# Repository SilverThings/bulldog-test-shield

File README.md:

# bulldog-test-shield
A testing shield for Bulldog testing for mocking real-world devices

Repository for .ino files, KiCad files, docs ...

# Prototype

Arduino Pro Mini clone BTE13-010 (3v3)

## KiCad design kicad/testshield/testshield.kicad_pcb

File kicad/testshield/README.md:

Only I2C is supported in this design. I am trying to find a way to fit raspberry, cubieboard and beaglebone with one connector. I'm not sure it's possible. Maybe with jumpers.

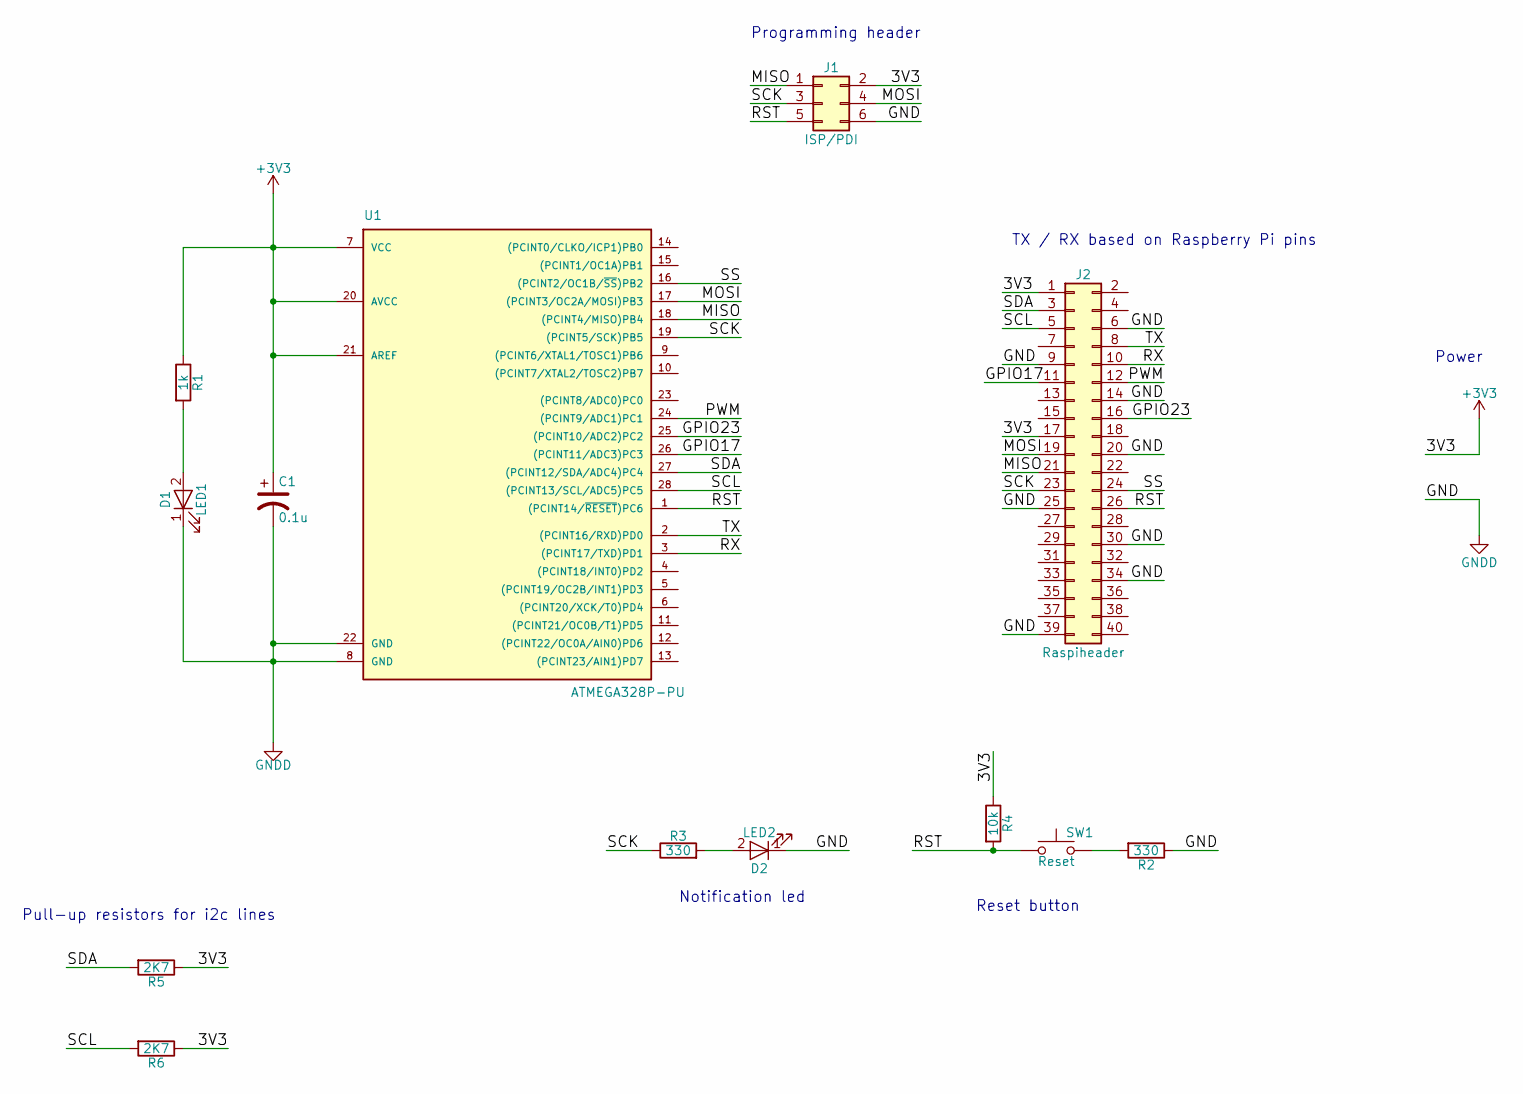
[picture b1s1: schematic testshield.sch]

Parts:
C1: 0.1u; c_elec_4x5.3
D1: LED1; LED_0805
D2: LED2; LED_0805
J1: ISP/PDI; Pin_Header_Straight_2x03
J2: Raspiheader; Pin_Header_Straight_2x20
R1: 1k; R_0603
R2, R3: 330; R_0603
R4: 10k; R_0603
R5, R6: 2K7; R_0603
SW1: Reset; SW_SPST_B3SL-1022P
U1: ATMEGA328P-PU; QFP80P900X900X120-32N

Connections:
+3V3: C1.1, J1.2, J2.1, J2.17, R1.1, R4.1, R5.1, R6.1, U1.7 (VCC), U1.20 (AVCC), U1.21 (AREF)
/GPIO17: J2.11, U1.26 ((PCINT11/ADC3)PC3)
/GPIO23: J2.16, U1.25 ((PCINT10/ADC2)PC2)
/MISO: J1.1, J2.21, U1.18 ((PCINT4/MISO)PB4)
/MOSI: J1.4, J2.19, U1.17 ((PCINT3/OC2A/MOSI)PB3)
/PWM: J2.12, U1.24 ((PCINT9/ADC1)PC1)
/RST: J1.5, J2.26, R4.2, SW1.1, U1.1 ((PCINT14/~RESET~)PC6)
/RX: J2.10, U1.3 ((PCINT17/TXD)PD1)
/SCK: J1.3, J2.23, R3.1, U1.19 ((PCINT5/SCK)PB5)
/SCL: J2.5, R6.2, U1.28 ((PCINT13/SCL/ADC5)PC5)
/SDA: J2.3, R5.2, U1.27 ((PCINT12/SDA/ADC4)PC4)
/SS: J2.24, U1.16 ((PCINT2/OC1B/~SS~)PB2)
/TX: J2.8, U1.2 ((PCINT16/RXD)PD0)
GNDD: C1.2, D1.1 (K), D2.1 (K), J1.6, J2.6, J2.9, J2.14, J2.20, J2.25, J2.30, J2.34, J2.39, R2.1, U1.8 (GND), U1.22 (GND)
unnamed: D1.2 (A), R1.2
unnamed: D2.2 (A), R3.2
unnamed: R2.2, SW1.2

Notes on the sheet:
TX / RX based on Raspberry Pi pins
Pull-up resistors for i2c lines
Programming header
Power
Reset button
Notification led

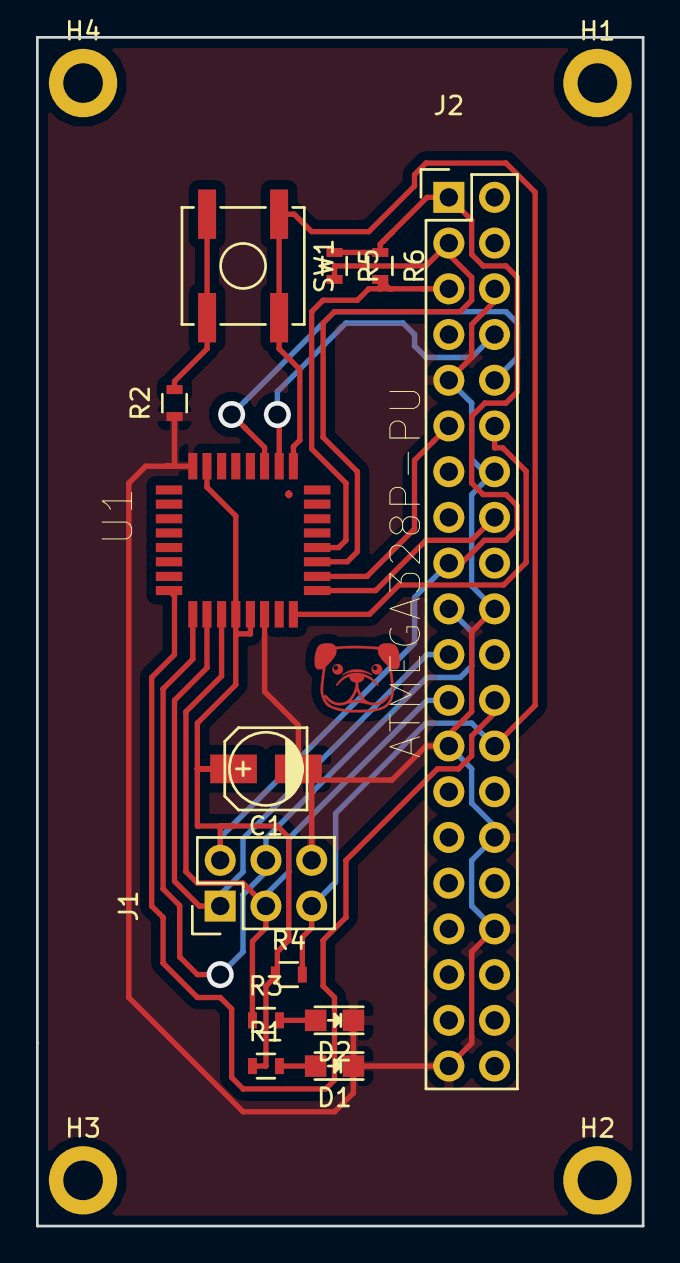
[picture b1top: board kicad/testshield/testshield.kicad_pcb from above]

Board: 2 copper layers, 33.7 x 66.0 mm, 17 parts (0 on the bottom side), 17 nets.

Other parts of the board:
H1, H2, H3, H4: MountingHole_2.2mm_M2_ISO14580_Pad

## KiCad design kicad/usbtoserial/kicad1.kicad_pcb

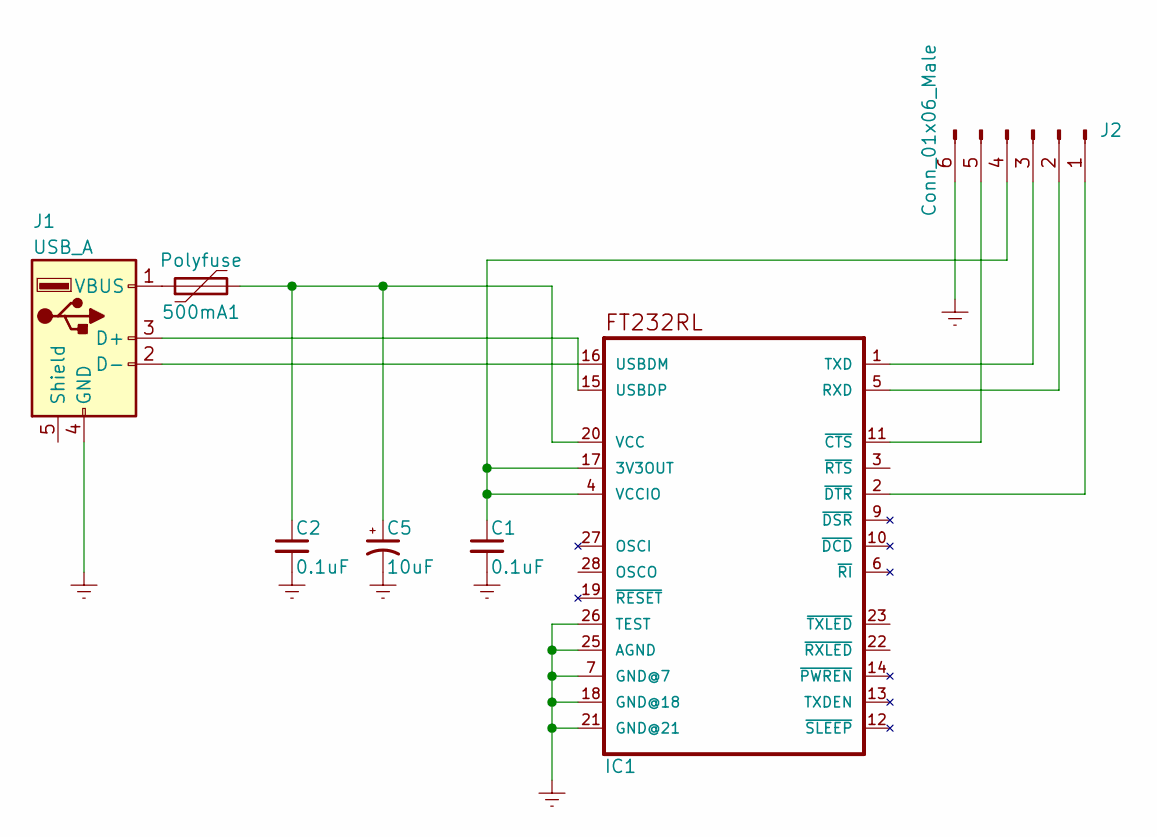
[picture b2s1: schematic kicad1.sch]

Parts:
500mA1: Polyfuse; Resistor_SMD+THTuniversal_0805to1206_RM10_HandSoldering
C1, C2: 0.1uF; C_0201
C5: 10uF; CP_Elec_3x5.3
IC1: FT232RL; SSOP28-LD
J1: USB_A; USB_Micro-B
J2: Conn_01x06_Male; Pin_Header_Angled_1x06_Pitch2.54mm

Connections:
Earth: C1.2, C2.2, C5.2, IC1.7 (GND@7), IC1.18 (GND@18), IC1.21 (GND@21), IC1.25 (AGND), IC1.26 (TEST), J1.4 (GND), J2.6
unnamed: 500mA1.1, J1.1 (VBUS)
unnamed: 500mA1.2, C2.1, C5.1, IC1.20 (VCC)
unnamed: C1.1, IC1.4 (VCCIO), IC1.17 (3V3OUT), J2.4
unnamed: IC1.1 (TXD), J2.3
unnamed: IC1.2 (~DTR~), J2.1
unnamed: IC1.5 (RXD), J2.2
unnamed: IC1.11 (~CTS~), J2.5
unnamed: IC1.15 (USBDP), J1.3 (D+)
unnamed: IC1.16 (USBDM), J1.2 (D-)

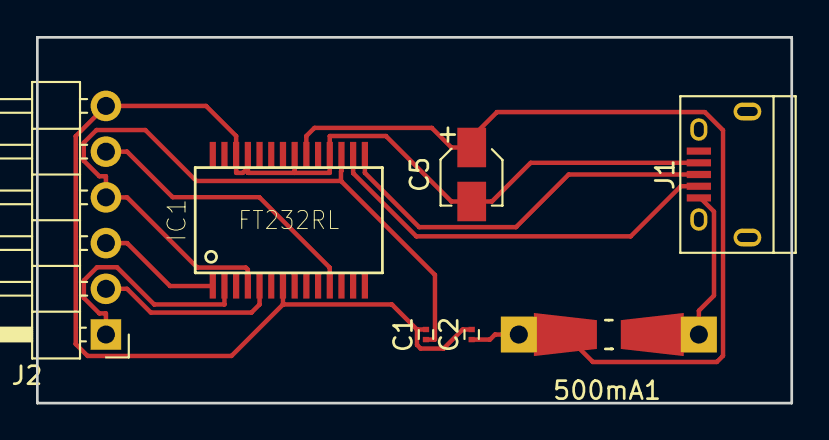
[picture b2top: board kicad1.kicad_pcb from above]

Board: 2 copper layers, 41.9 x 20.3 mm, 7 parts (0 on the bottom side), 10 nets.

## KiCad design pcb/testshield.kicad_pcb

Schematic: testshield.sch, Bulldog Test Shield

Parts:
C1: 100uF; CP_Tantalum_Case-D_EIA-7343-31_Hand
C2, C3, C4, C5: 100nF; C_0805_HandSoldering
D1: LED1; LED_0805_HandSoldering
D2: LED2; LED_0805_HandSoldering
D3: LED3; LED_0805_HandSoldering
J1: ISP 6 pin; Pin_Header_Straight_2x03
J2: Raspiheader; Pin_Header_Straight_2x20
R1, R2, R3: 68; R_0805_HandSoldering
R4: 10k; R_0805_HandSoldering
R5, R6: 2K7; R_0805_HandSoldering
R7, R8, R9: 330; R_0805_HandSoldering
SW1: Reset; SW_SPST_B3S-1000
U1: ATMEGA328P-AU; TQFP-32_7x7mm_Pitch0.8mm

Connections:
+3V3: C1.1, C2.2, C3.2, C4.2, J1.2, J2.1, J2.17, R1.1, R4.1, R5.1, R6.1, U1.4 (VCC), U1.6 (VCC), U1.18 (AVCC)
/GPIO17: J2.11, U1.26 ((PCINT11/ADC3)PC3)
/LED: R3.1, U1.12 ((PCINT0/CLKO/ICP1)PB0)
/MISO: J1.1, R8.2, U1.16 ((PCINT4/MISO)PB4)
/MOSI: J1.4, R7.1, U1.15 ((PCINT3/OC2A/MOSI)PB3)
/PWMa: J2.16, U1.1 ((PCINT19/OC2B/INT1)PD3)
/PWMp: J2.12, U1.25 ((PCINT10/ADC2)PC2)
/RST: J1.5, J2.26, R4.2, SW1.1, U1.29 ((PCINT14/~RESET~)PC6)
/RX: J2.10, U1.31 ((PCINT17/TXD)PD1)
/SCK: J1.3, R2.1, R9.2, U1.17 ((PCINT5/SCK)PB5)
/SCL: J2.5, R6.2, U1.28 ((PCINT13/SCL/ADC5)PC5)
/SDA: J2.3, R5.2, U1.27 ((PCINT12/SDA/ADC4)PC4)
/SS: J2.24, U1.14 ((PCINT2/OC1B/~SS~)PB2)
/TX: J2.8, U1.30 ((PCINT16/RXD)PD0)
GNDD: C1.2, C2.1, C3.1, C4.1, C5.1, D1.1, D2.1, D3.1, J1.6, J2.6, J2.9, J2.14, J2.20, J2.25, J2.30, J2.34, J2.39, SW1.2, U1.3 (GND), U1.5 (GND), U1.21 (GND)
unnamed: C5.2, U1.20 (AREF)
unnamed: D1.2, R1.2
unnamed: D2.2, R2.2
unnamed: D3.2, R3.2
unnamed: J2.19, R7.2
unnamed: J2.21, R8.1
unnamed: J2.23, R9.1

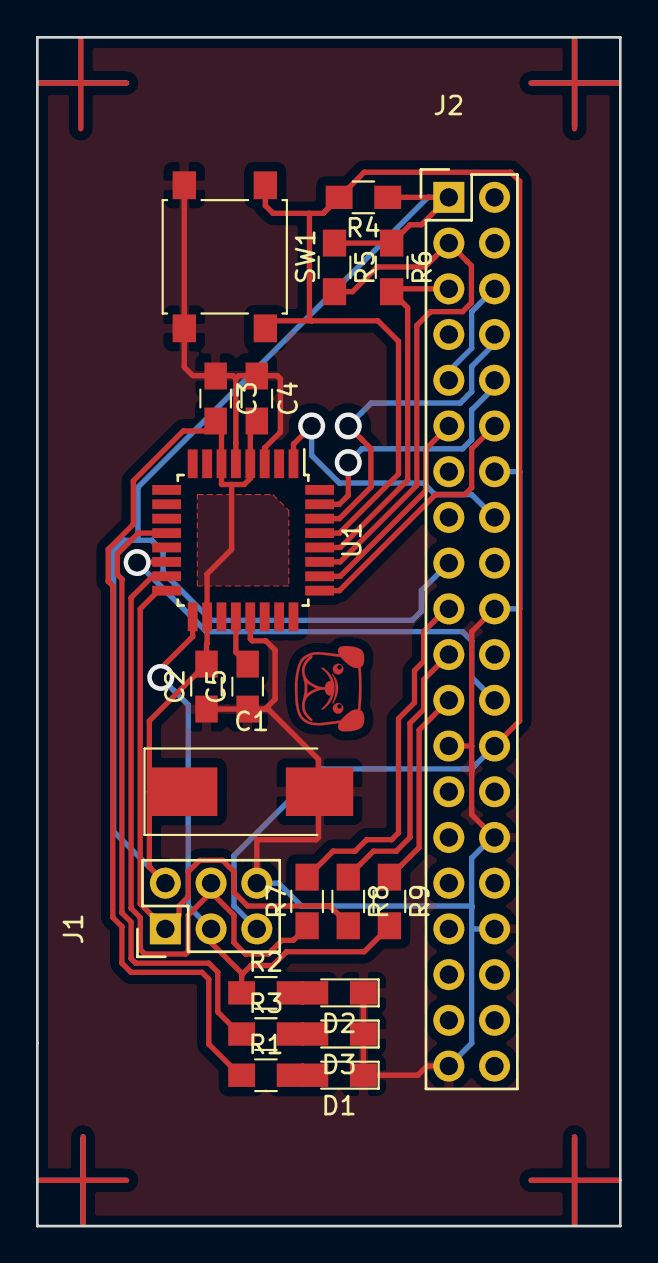
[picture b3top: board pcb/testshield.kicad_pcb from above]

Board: 2 copper layers, 32.4 x 66.0 mm, 21 parts (0 on the bottom side), 22 nets.

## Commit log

2017-12-14 added initial arduino files
2017-12-21 added prototype pics
2018-02-08 added noop
2018-02-08 fix int to byte issue
2018-02-14 Create tmp
2018-02-14 routing in 1 layer
2018-03-27 added serial debug messages
2018-03-27 added makefile
2018-04-11 big change to the code, now using registers for i2c
2018-04-11 kicad linux update
2018-04-11 simplification of schema with labels, WIP
2018-04-11 further simplification, still WIP
2018-04-13 pcb layout WIP
2018-04-13 pcb routes WIP
2018-04-13 pcb layout done
    v1.0
2018-04-17 updated board
    added decoupling caps
    added miso mosi sck resistors
    updated footprints
2018-04-22 now using millis instead of delay
2018-04-23 modified i2c functionality
2018-04-26 added burn script and config files
2018-04-27 changed PWM pins, changed reset pullup placement
2018-04-27 created layout PDFs
2018-05-18 changed dir structure
2018-05-18 moved kicad files
2018-05-18 rename kicad dir
